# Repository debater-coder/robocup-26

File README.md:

# Team High Scorers RoboCup 2026 Repository

This is the monorepo for the High Scorers RoboCup Junior Opens Soccer team. When browsing code,
it is highly recommended to browse in an editor with "Go to definition" support. If you are viewing from
GitHub, press the `.` key to open in an online VSCode instance.

[**Onshape CAD here**](https://cad.onshape.com/documents/ea45f627640093c41ce29f68/w/55dbcc8e0fa51676d6d22381/e/4ebe9911eb0a9aed26b8f2e8?renderMode=0&uiState=6aed85551ba35b1558f578c4)

## Project structure

## License

All software in this repository is licensed under the [MIT license](./LICENSE).
Hardware (including the PCB under `motor-controller-pcb/` and the CAD export at
`Main Assembly.step`) are under the CERN OHL-P (permissive).

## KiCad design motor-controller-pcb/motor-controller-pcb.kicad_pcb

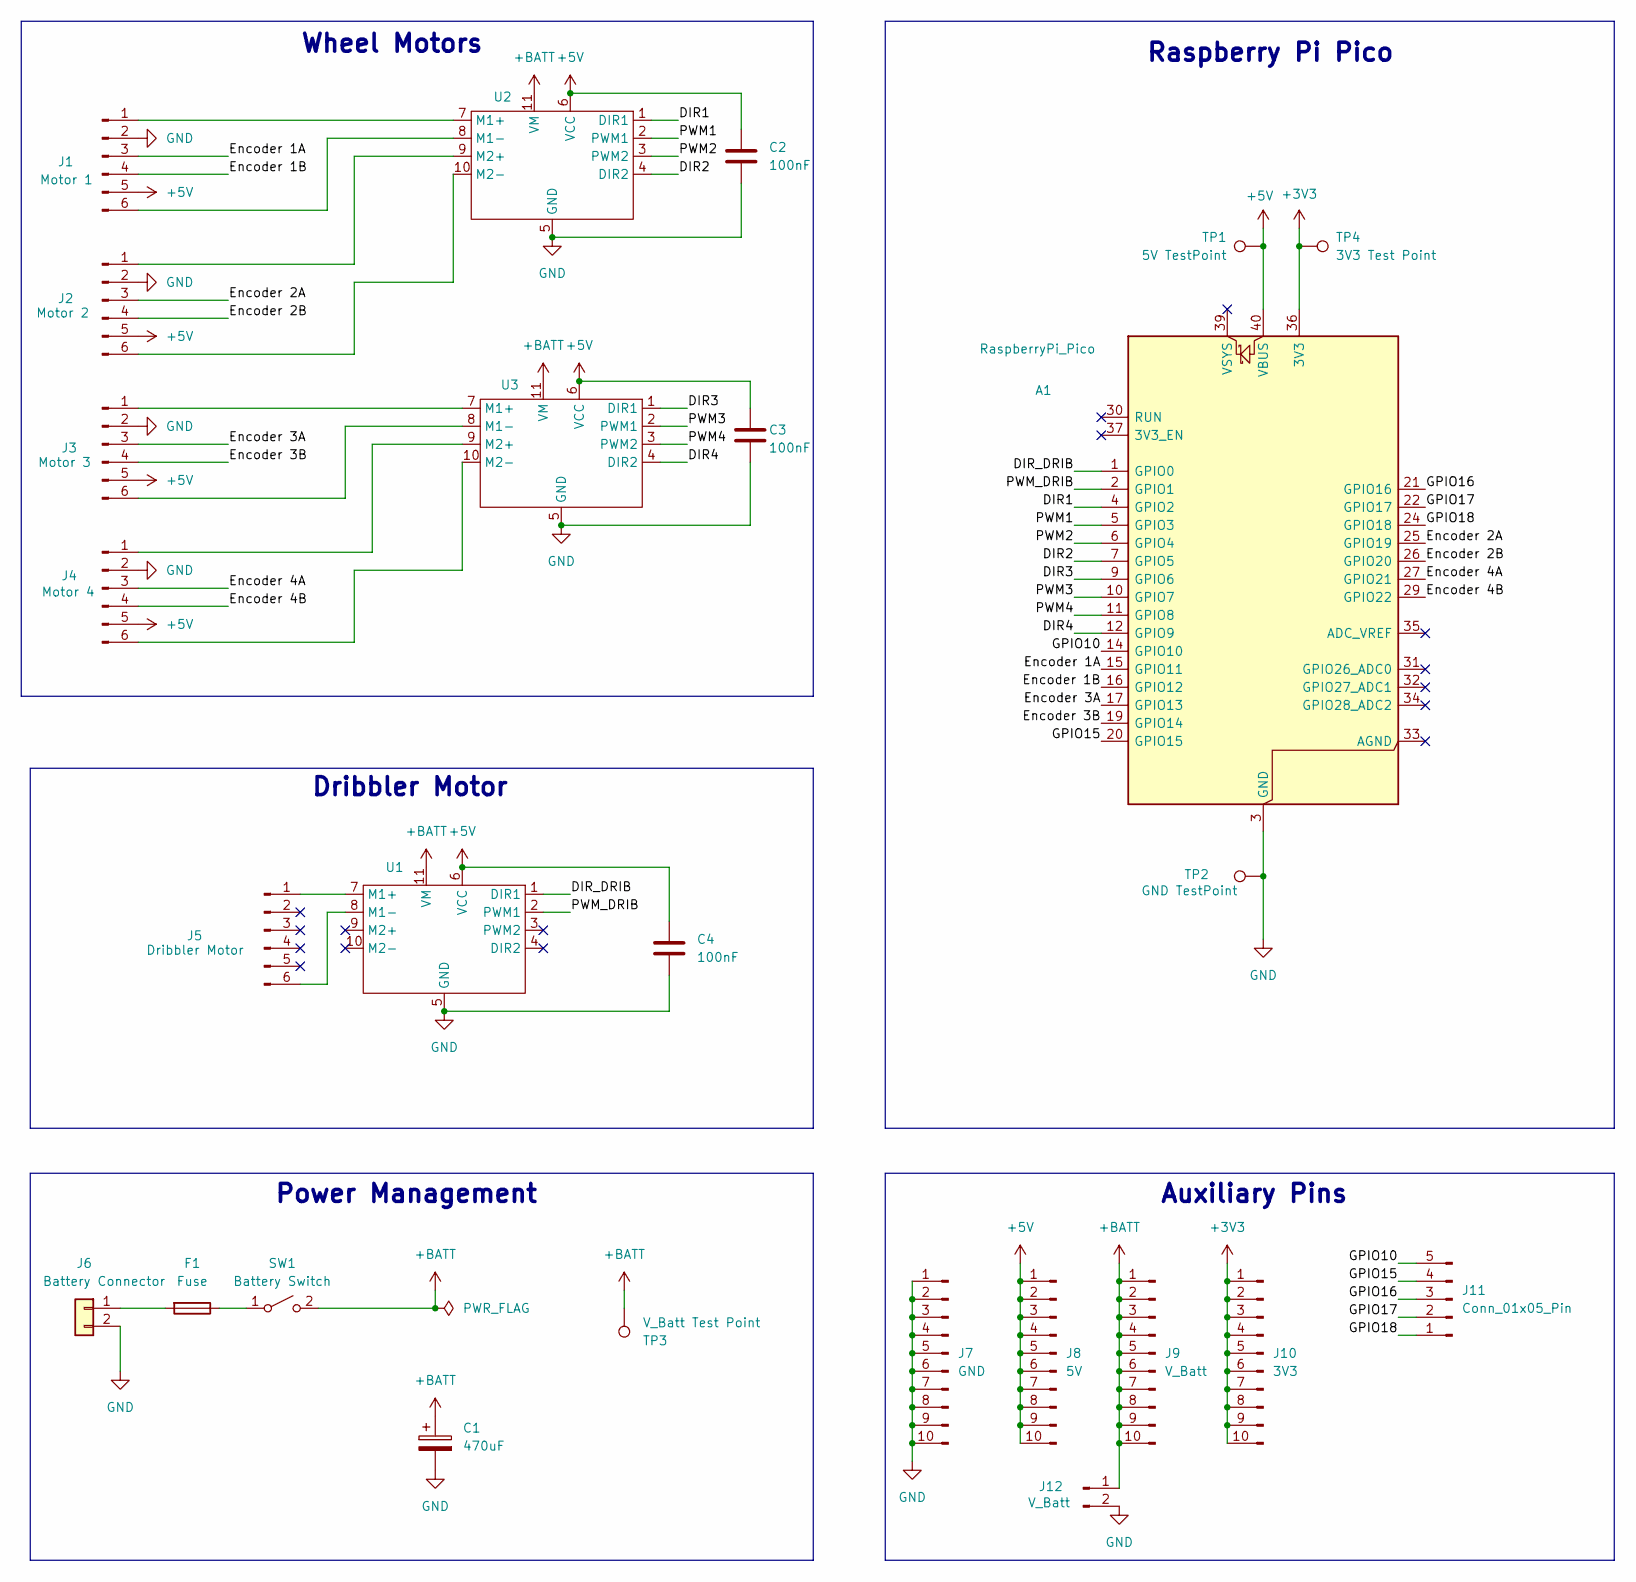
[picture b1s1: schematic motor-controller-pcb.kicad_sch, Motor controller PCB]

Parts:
A1: RaspberryPi_Pico; RaspberryPi_Pico_Common_Unspecified
C1: 470uF; CP_Radial_D8.0mm_P3.50mm
C2, C3, C4: 100nF; C_0805_2012Metric
F1: Fuse; Fuseholder_Clip-5x20mm_Littelfuse_100_Inline_P20.50x4.60mm_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
J1: Motor 1; JST_PH_B6B-PH-K_1x06_P2.00mm_Vertical
J2: Motor 2; JST_PH_B6B-PH-K_1x06_P2.00mm_Vertical
J3: Motor 3; JST_PH_B6B-PH-K_1x06_P2.00mm_Vertical
J4: Motor 4; JST_PH_B6B-PH-K_1x06_P2.00mm_Vertical
J5: Dribbler Motor; JST_PH_B6B-PH-K_1x06_P2.00mm_Vertical
J6: Battery Connector; SolderWire-4sqmm_1x02_P12mm_D3mm_OD6mm_Relief
J7: GND; PinHeader_1x10_P2.54mm_Vertical
J8: 5V; PinHeader_1x10_P2.54mm_Vertical
J9: V_Batt; PinHeader_1x10_P2.54mm_Vertical
J10: 3V3; PinHeader_1x10_P2.54mm_Vertical
J11: Conn_01x05_Pin; PinHeader_1x05_P2.54mm_Vertical
J12: V_Batt; TerminalBlock_MaiXu_MX126-5.0-02P_1x02_P5.00mm
SW1: Battery Switch; SolderWire-4sqmm_1x02_P12mm_D3mm_OD6mm_Relief
TP1: 5V TestPoint; TestPoint_Pad_1.5x1.5mm
TP2: GND TestPoint; TestPoint_Pad_1.5x1.5mm
TP3: V_Batt Test Point; TestPoint_Pad_1.5x1.5mm
TP4: 3V3 Test Point; TestPoint_Pad_1.5x1.5mm
U1, U2, U3: DRI0044

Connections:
+3V3: A1.36 (3V3), J10.1, J10.2, J10.3, J10.4, J10.5, J10.6, J10.7, J10.8, J10.9, J10.10, TP4.1
+5V: A1.40 (VBUS), C2.1, C3.1, C4.1, J1.5, J2.5, J3.5, J4.5, J8.1, J8.2, J8.3, J8.4, J8.5, J8.6, J8.7, J8.8, J8.9, J8.10, TP1.1, U1.6 (VCC), U2.6 (VCC), U3.6 (VCC)
+BATT: C1.1, J9.1, J9.2, J9.3, J9.4, J9.5, J9.6, J9.7, J9.8, J9.9, J9.10, J12.1, SW1.2 (B), TP3.1, U1.11 (VM), U2.11 (VM), U3.11 (VM)
/DIR1: A1.4 (GPIO2), U2.1 (DIR1)
/DIR2: A1.7 (GPIO5), U2.4 (DIR2)
/DIR3: A1.9 (GPIO6), U3.1 (DIR1)
/DIR4: A1.12 (GPIO9), U3.4 (DIR2)
/DIR_DRIB: A1.1 (GPIO0), U1.1 (DIR1)
/Encoder 1A: A1.15 (GPIO11), J1.3
/Encoder 1B: A1.16 (GPIO12), J1.4
/Encoder 2A: A1.25 (GPIO19), J2.3
/Encoder 2B: A1.26 (GPIO20), J2.4
/Encoder 3A: A1.17 (GPIO13), J3.3
/Encoder 3B: A1.19 (GPIO14), J3.4
/Encoder 4A: A1.27 (GPIO21), J4.3
/Encoder 4B: A1.29 (GPIO22), J4.4
/GPIO10: A1.14 (GPIO10), J11.5
/GPIO15: A1.20 (GPIO15), J11.4
/GPIO16: A1.21 (GPIO16), J11.3
/GPIO17: A1.22 (GPIO17), J11.2
/GPIO18: A1.24 (GPIO18), J11.1
/PWM1: A1.5 (GPIO3), U2.2 (PWM1)
/PWM2: A1.6 (GPIO4), U2.3 (PWM2)
/PWM3: A1.10 (GPIO7), U3.2 (PWM1)
/PWM4: A1.11 (GPIO8), U3.3 (PWM2)
/PWM_DRIB: A1.2 (GPIO1), U1.2 (PWM1)
GND: A1.3 (GND), A1.8 (GND), A1.13 (GND), A1.18 (GND), A1.23 (GND), A1.28 (GND), A1.38 (GND), C1.2, C2.2, C3.2, C4.2, J1.2, J2.2, J3.2, J4.2, J6.2, J7.1, J7.2, J7.3, J7.4, J7.5, J7.6, J7.7, J7.8, J7.9, J7.10, J12.2, TP2.1, U1.5 (GND), U2.5 (GND), U3.5 (GND)
unnamed: J1.1, U2.7 (M1+)
unnamed: J1.6, U2.8 (M1-)
unnamed: J2.1, U2.9 (M2+)
unnamed: J2.6, U2.10 (M2-)
unnamed: J3.1, U3.7 (M1+)
unnamed: J3.6, U3.8 (M1-)
unnamed: J4.1, U3.9 (M2+)
unnamed: J4.6, U3.10 (M2-)
unnamed: J5.1, U1.7 (M1+)
unnamed: J5.6, U1.8 (M1-)
unnamed: F1.2, J6.1
unnamed: F1.1, SW1.1 (A)

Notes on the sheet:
Raspberry Pi Pico
Dribbler Motor
Auxiliary Pins
Power Management
Wheel Motors

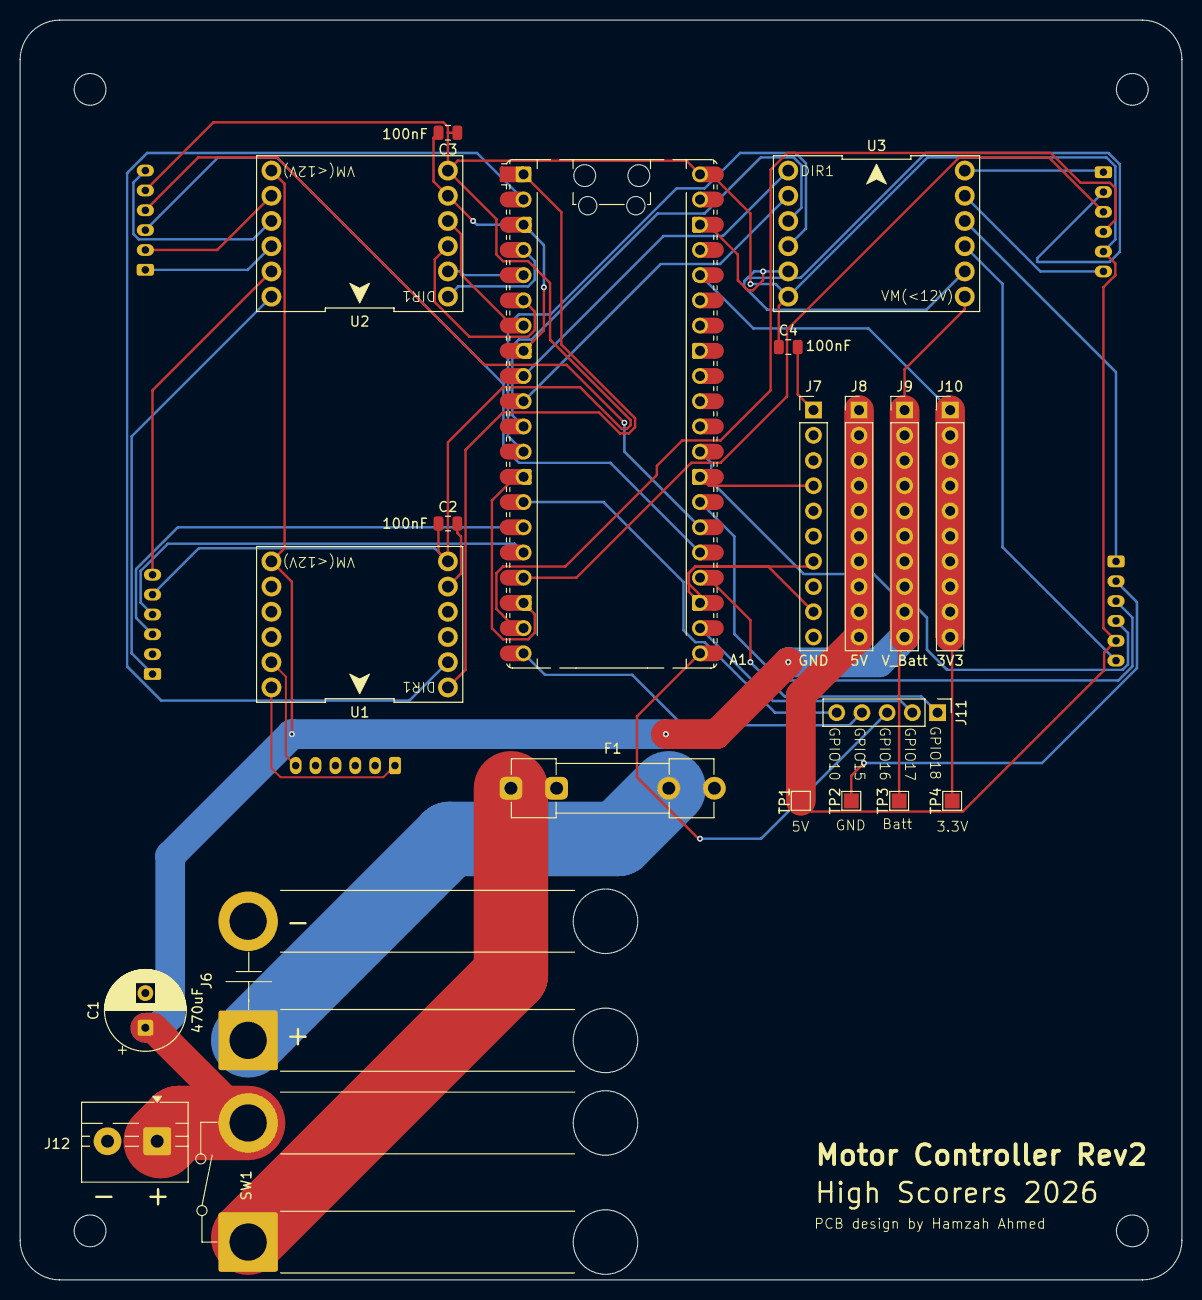
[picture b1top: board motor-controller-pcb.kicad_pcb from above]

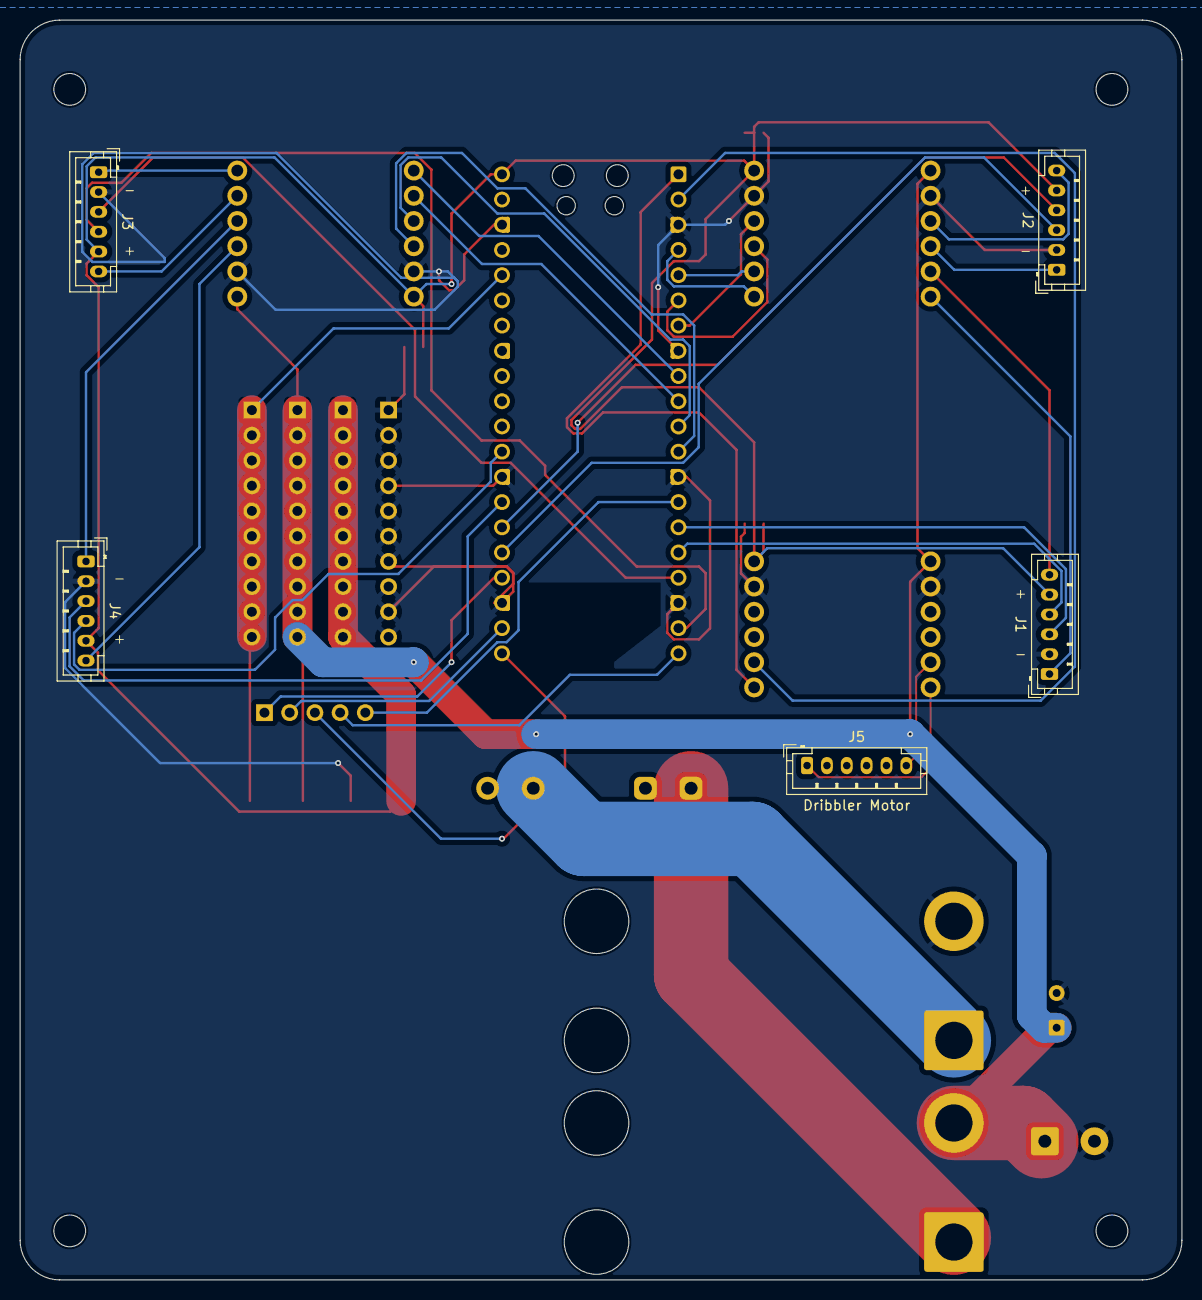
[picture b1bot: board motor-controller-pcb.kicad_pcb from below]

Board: 2 copper layers, 117.0 x 126.9 mm, 26 parts (5 on the bottom side), 39 nets.

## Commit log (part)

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2025-08-29 feat: working NixOS test config
2025-08-30 feat: add nixos-hardware
2025-10-23 docs: fix typo in nixos README.md
2025-10-27 feat: initial picam config
2025-10-27 feat: lower python version
2025-10-27 fix: change shell hook
2025-10-28 docs
2025-10-28 feat: initial ball detection
2025-10-28 fix: only import cv2 typing when typechecking
2025-10-28 fix: change blur size
2025-10-28 fix: detect vaguely orange
2025-10-28 feat: add utility
2025-10-28 fix: typo
2025-10-29 feat: better orange params
2025-11-03 fix: flip camera
2025-11-03 fix: flip
2025-11-07 feat: echo test for pico
2025-11-07 feat: add rshell to pico
2025-11-07 feat: move nix shell to root
2025-11-07 Revert "feat: move nix shell to root"
    This reverts commit 53ac8a4ac7660d13246b166669ca4fb2130b2cc9.
2025-11-07 Revert "feat: add rshell to pico"
    This reverts commit bd0b26686dfb8c57506edc8fa4abe32e96ba4601.
2025-11-08 feat: switch to rust for pico
2025-11-08 feat: test
2025-11-08 usb blink
2025-11-08 feat: usb logging with blinky
2025-11-08 feat: dual serial ports for command and logging
2025-11-09 feat: basic one way rpc
2025-11-09 feat: rpc with request and response
2025-11-09 feat: use watchdog to automatically recover after failures
2025-11-12 chore
2025-11-12 fix: add cargo to flake
2025-11-21 feat: led for normal pico
2026-02-03 pico motor
2026-02-04 feat: report odom
2026-02-05 feat: pid motor control
2026-02-19 pcb work
2026-02-20 feat: visualiser sprites
2026-03-03 fix: change pcb footprint to jst ph
2026-03-05 feat: schematic improvement
2026-03-05 feat: capacitors and aux pins
2026-03-05 feat: pcb layout
2026-03-06 feat: final
2026-03-07 feat: pcb prettification
2026-03-08 fix: make wire strain relief holes large enough
2026-03-15 feat: encoder and blinky tests
2026-03-16 feat: integrate quadrature encoder into main
2026-04-01 rerun test
2026-04-01 remove envrc from controller
2026-04-02 redo controller
2026-04-05 start simulator
2026-04-05 feat: simulator register and kickoff
2026-04-05 feat: field model for added realism
2026-04-06 feat: world snapshots
2026-04-06 fix: log robot directions
2026-04-06 feat: submit commands to sim
2026-04-06 feat: walls around field
2026-04-06 feat: working goal scoring
2026-04-06 feat: exit when simulation complete
2026-04-22 chore(deps): bump rand from 0.8.5 to 0.8.6 in /simulator
    Bumps [rand](https://github.com/rust-random/rand) from 0.8.5 to 0.8.6.
    - [Release notes](https://github.com/rust-random/rand/releases)
    - [Changelog](https://github.com/rust-random/rand/blob/0.8.6/CHANGELOG.md)
    - [Commits](https://github.com/rust-random/rand/compare/0.8.5...0.8.6)
    ---
    updated-dependencies:
2026-04-24 chore(deps): bump rustls-webpki from 0.103.10 to 0.103.13 in /simulator
    Bumps [rustls-webpki](https://github.com/rustls/webpki) from 0.103.10 to 0.103.13.
    - [Release notes](https://github.com/rustls/webpki/releases)
    - [Commits](https://github.com/rustls/webpki/compare/v/0.103.10...v/0.103.13)
    ---
    updated-dependencies:
    - dependency-name: rustls-webpki
2026-04-28 debug
2026-04-29 fix: reverse motor direction
2026-04-30 feat: fix all motor directions
2026-05-04 feat: pid control of individual motors
2026-05-05 fix: odom
2026-05-06 wip: feedforward + watch (multiple consumer channel)
2026-05-07 feat: make feedforward term good
2026-05-07 feat: kinematics
2026-05-07 fix: encoder at higher clock rate
2026-05-11 chore(deps): bump urllib3 from 2.6.3 to 2.7.0 in /controller
    Bumps [urllib3](https://github.com/urllib3/urllib3) from 2.6.3 to 2.7.0.
    - [Release notes](https://github.com/urllib3/urllib3/releases)
    - [Changelog](https://github.com/urllib3/urllib3/blob/main/CHANGES.rst)
    - [Commits](https://github.com/urllib3/urllib3/compare/2.6.3...2.7.0)
    ---
    updated-dependencies:
2026-05-12 fix: actually clamp speed sent to motor
2026-05-14 fix: logging and remove double pulse conversion
2026-05-14 feat: tune pid
2026-05-15 feat: return displacement of chassis
2026-05-17 feat: controller-pico interop
2026-05-19 chore(deps): bump idna from 3.11 to 3.15 in /controller
    Bumps [idna](https://github.com/kjd/idna) from 3.11 to 3.15.
    - [Release notes](https://github.com/kjd/idna/releases)
    - [Changelog](https://github.com/kjd/idna/blob/master/HISTORY.md)
    - [Commits](https://github.com/kjd/idna/compare/v3.11...v3.15)
    ---
    updated-dependencies:
2026-05-20 feat: motion testing
2026-05-24 feat: deliberate compiler error for TODO
2026-05-25 fix: nix flake
2026-05-25 feat
2026-05-25 feat: camera streamer
2026-05-25 rerun config
2026-06-01 fix: rotate camera and slow framerate
2026-06-01 fix: connect to central sever
2026-06-01 fix: compress
2026-06-01 fix: rgb image to jpg
2026-06-04 feat: camera behaviour
2026-06-04 feat: started
2026-06-05 fea: rerun flake (control rerun version)
2026-06-18 stub: ball chase
2026-06-26 chase ball
2026-06-26 fix typo
2026-06-29 fixes
2026-06-29 feat: hard cutoff
2026-06-30 feat: command timeout
2026-06-30 feat: initial c linking
